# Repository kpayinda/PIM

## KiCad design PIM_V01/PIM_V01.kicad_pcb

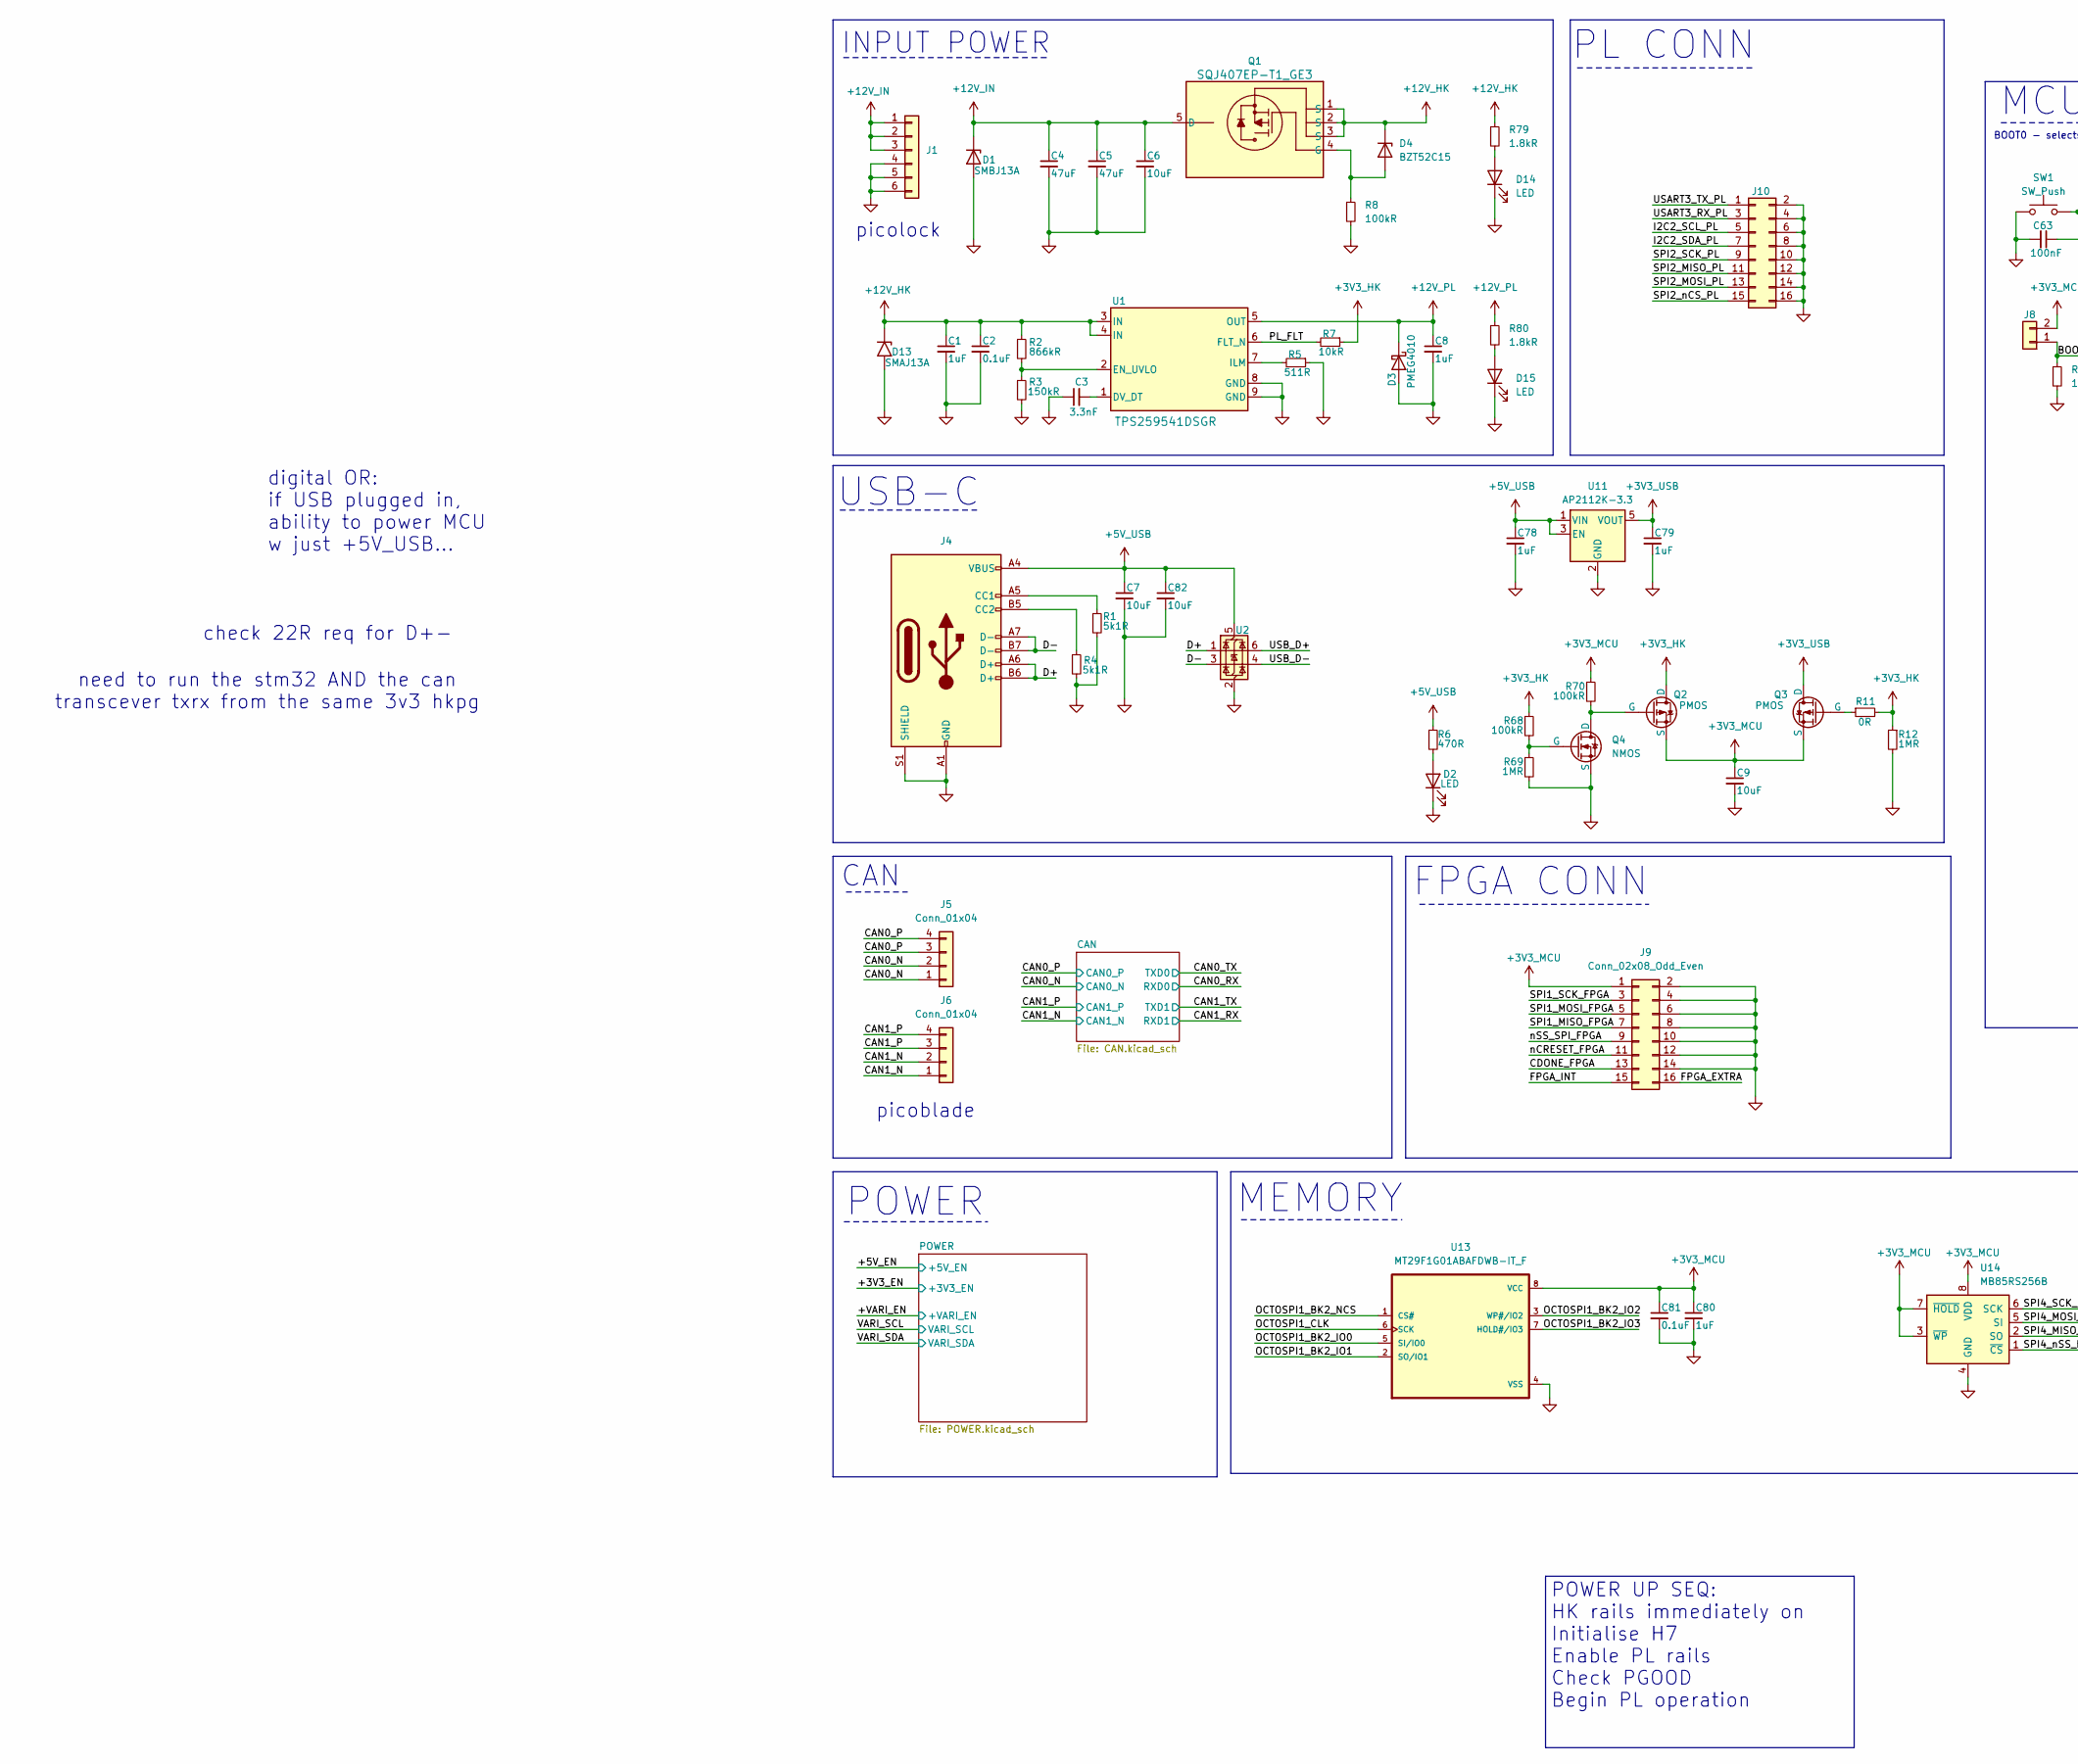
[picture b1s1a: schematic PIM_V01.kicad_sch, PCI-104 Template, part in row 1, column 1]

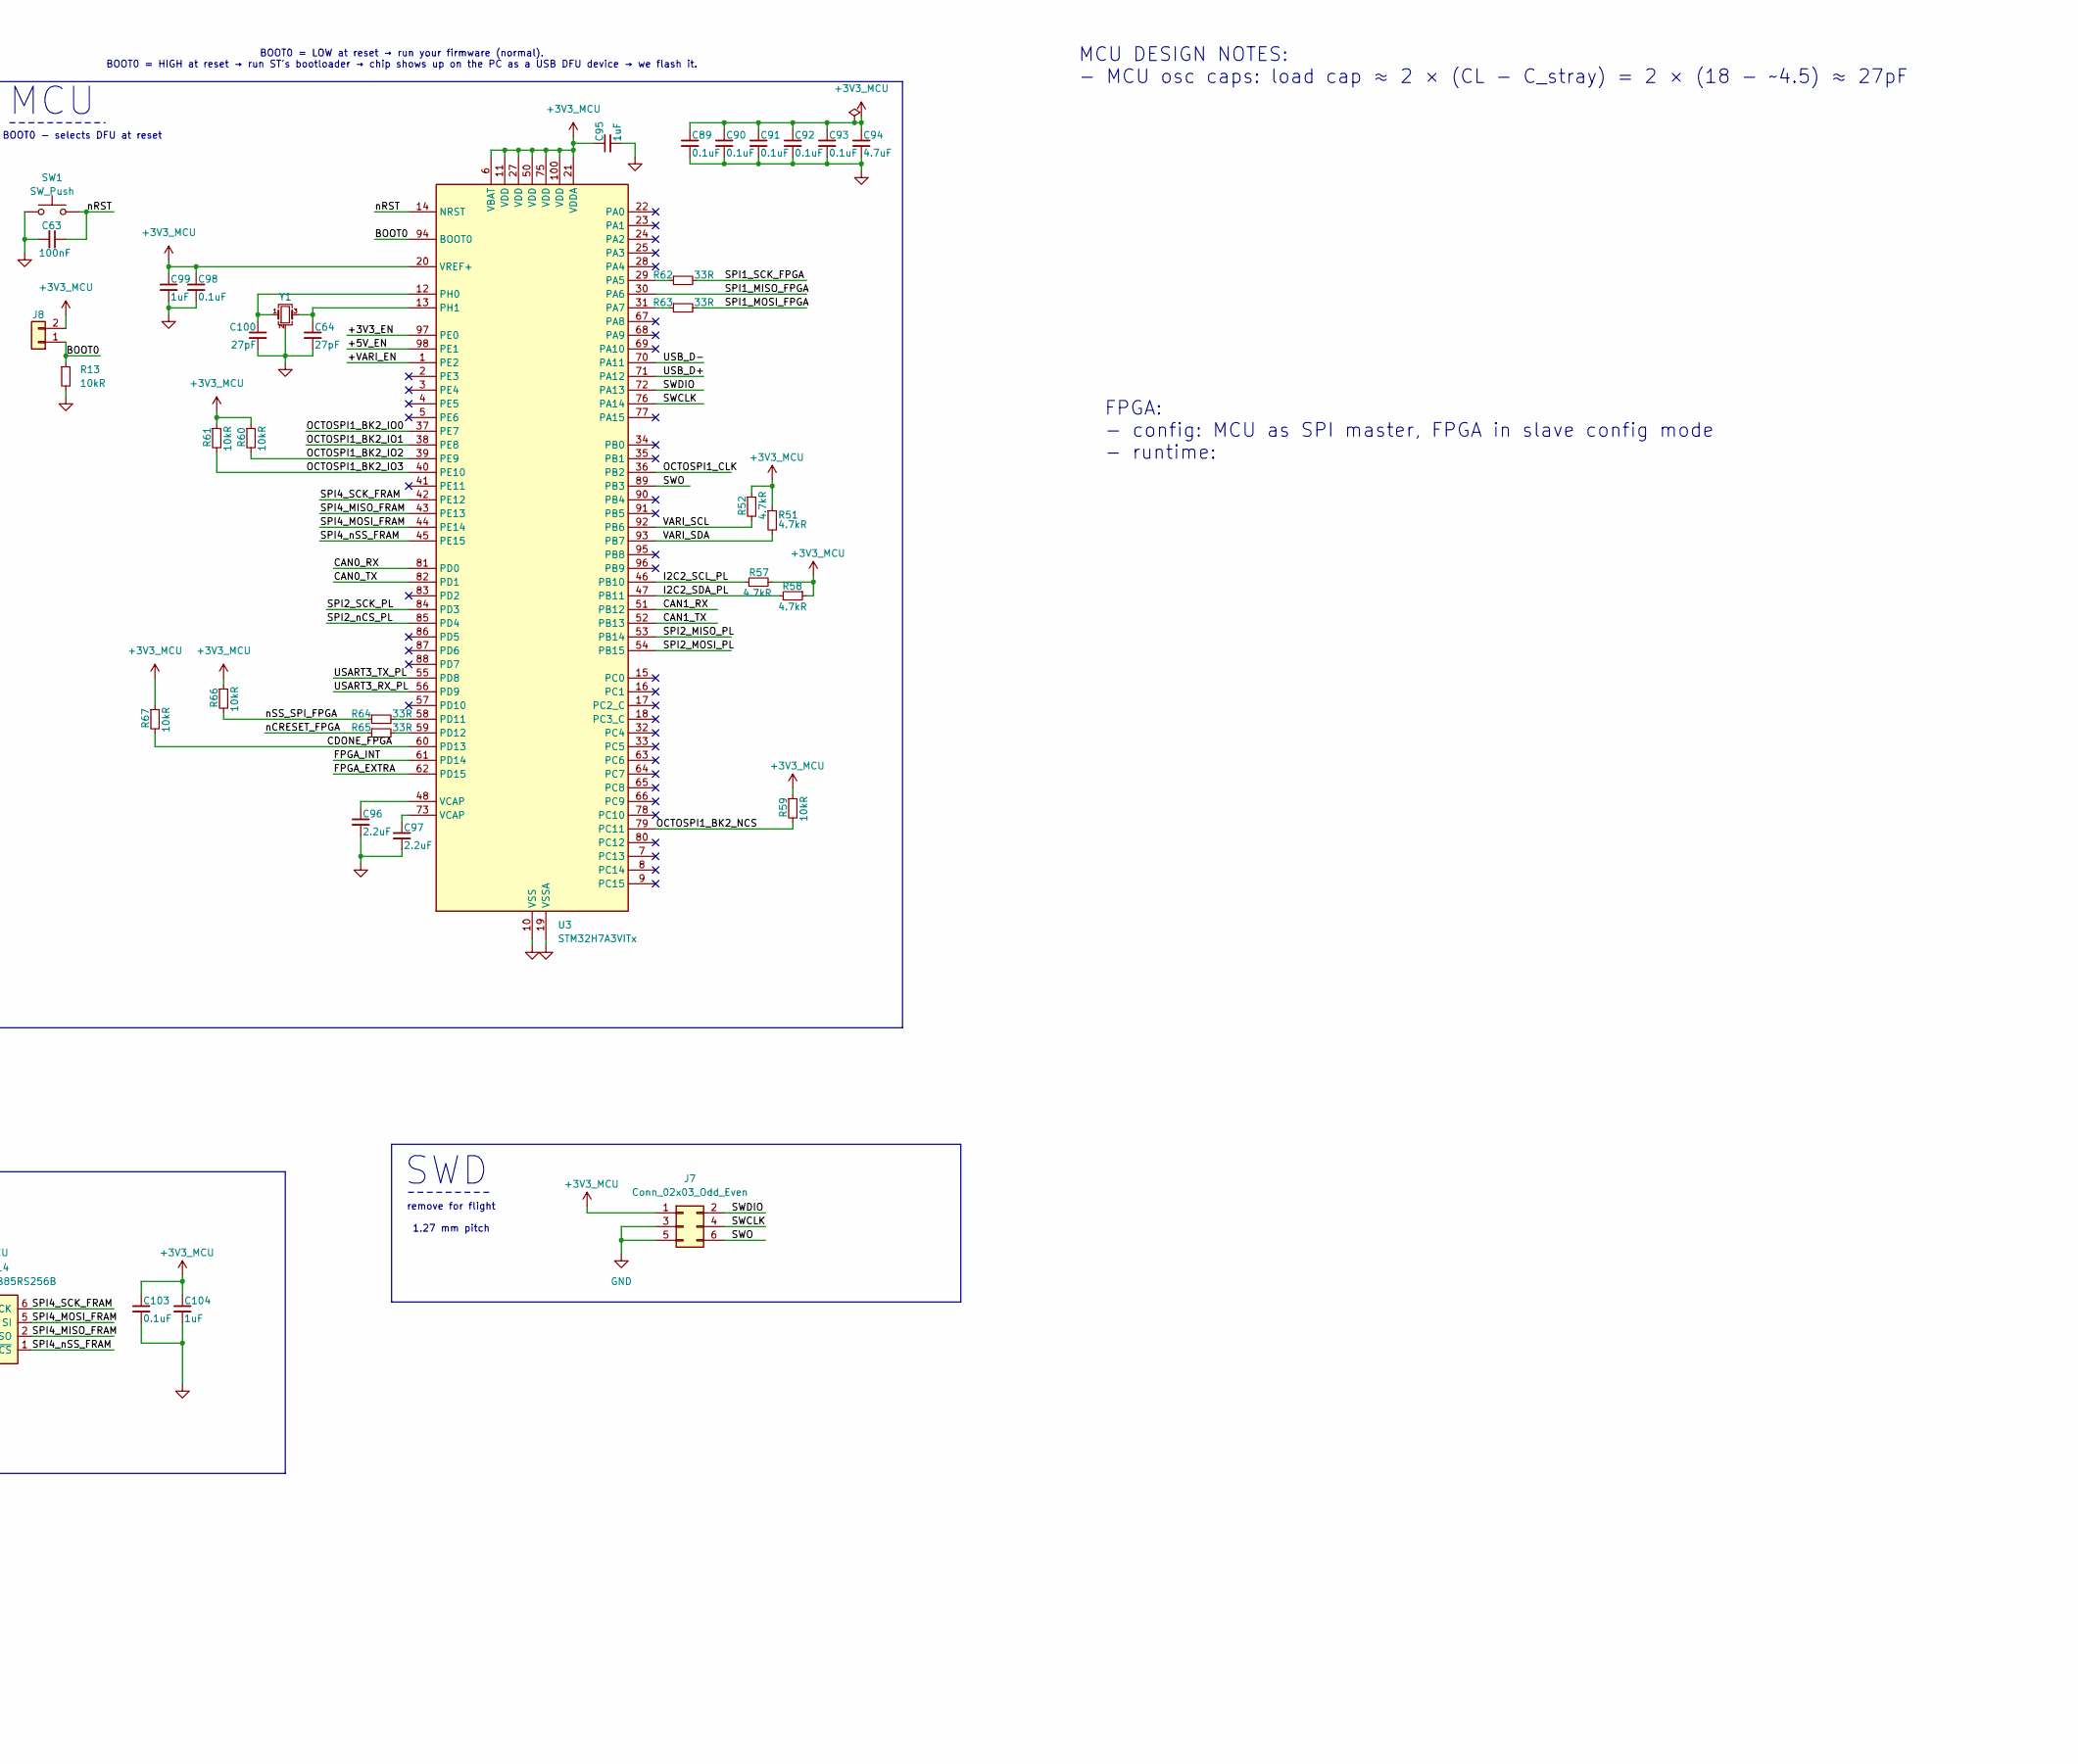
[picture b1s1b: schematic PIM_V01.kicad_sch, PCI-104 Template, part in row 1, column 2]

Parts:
C1, C8, C78, C79, C80, C95, C99, C104: 1uF; C_0603_1608Metric
C2, C81, C89, C90, C91, C92, C93, C98, C103: 0.1uF; C_0603_1608Metric
C3: 3.3nF; C_0603_1608Metric
C4, C5: 47uF; C_0603_1608Metric; Rating 50V, MLCC
C6, C7, C9, C82: 10uF; C_0603_1608Metric
C63: 100nF; C_0603_1608Metric
C64, C100: 27pF; C_0603_1608Metric
C94: 4.7uF; C_0603_1608Metric
C96, C97: 2.2uF; C_0603_1608Metric
D1: SMBJ13A; SMBJ16A; MPN SMBJ13A
D2: LED; LED_0603_1608Metric
D3: PMEG4010; Nexperia_CFP3_SOD-123W; MPN PMEG4010ER,115
D4: BZT52C15; Nexperia_CFP3_SOD-123W
D13: SMAJ13A; D_SMA; MPN SMAJ13A
D14, D15: LED; LED_0603_1608Metric; MPN XL-1608PGC-06
J1: Conn_01x06; Molex_Pico-Lock_504050-0691_1x06-1MP_P1.50mm_Horizontal; MPN 5040500691
J4: USB_C_Receptacle_USB2.0_14P; USB_C_Receptacle_HCTL_HC-TYPE-C-16P-01A
J5, J6: Conn_01x04; Molex_PicoBlade_53261-0471_1x04-1MP_P1.25mm_Horizontal
J7: Conn_02x03_Odd_Even; PinHeader_2x03_P2.54mm_Vertical
J8: Conn_01x02; PinHeader_1x02_P2.54mm_Vertical
J9, J10: Conn_02x08_Odd_Even; PinHeader_2x08_P2.54mm_Vertical
Q1: SQJ407EP-T1_GE3; PowerPAK-SO-8L_Option-2_VIS
Q2, Q3: PMOS; SOT-23-3; MPN DMG2305UX-7
Q4: NMOS; SOT-23-3
R1, R4: 5k1R; R_0603_1608Metric
R2: 866kR; R_0603_1608Metric
R3: 150kR; R_0603_1608Metric
R5: 511R; R_0603_1608Metric
R6: 470R; R_0603_1608Metric
R7, R13, R59, R60, R61, R66, R67: 10kR; R_0603_1608Metric
R8, R68, R70: 100kR; R_0603_1608Metric
R11: 0R; R_0603_1608Metric
R12, R69: 1MR; R_0603_1608Metric
R51, R52, R57, R58: 4.7kR; R_0603_1608Metric
R62, R63, R64, R65: 33R; R_0603_1608Metric
R79, R80: 1.8kR; R_0603_1608Metric
SW1: SW_Push; SW_SPST_B3U-1000P
U1: TPS259541DSGR; DSG0008A; MPN TPS259541DSGR
U2: USBLC6-2SC6; SOT-23-6
U3: STM32H7A3VITx; LQFP-100_14x14mm_P0.5mm
U11: AP2112K-3.3; SOT-23-5
U13: MT29F1G01ABAFDWB-IT_F; WSON-8-1EP_8x6mm_P1.27mm_EP3.4x4.3mm; PARTREV LTR
U14: MB85RS256B; JEITA_SOIC-8_3.9x4.9mm_P1.27mm
Y1: Crystal_GND24_Small; Crystal_SMD_Abracon_ABM8G-4Pin_3.2x2.5mm

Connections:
+3V3_HK: Q2.1 (D), R7.1, R11.2, R12.1, R68.1; also elsewhere on the board
+3V3_MCU: C9.1, C80.1, C81.1, C89.1, C90.1, C91.1, C92.1, C93.1, C94.1, C95.1, C98.1, C99.1, C103.1, C104.1, J7.1, J8.2, J9.1, Q2.3 (S), Q3.3 (S), R51.1, R52.1, R57.2, R58.1, R59.1, R60.1, R61.1, R66.1, R67.1, R70.1, U3.6 (VBAT), U3.11 (VDD), U3.20 (VREF+), U3.21 (VDDA), U3.27 (VDD), U3.50 (VDD), U3.75 (VDD), U3.100 (VDD), U13.8 (VCC), U14.3 (~WP), U14.7 (~HOLD), U14.8 (VDD)
+3V3_USB: C79.1, Q3.1 (D), U11.5 (VOUT)
+5V_USB: C7.1, C78.1, C82.1, J4.A4 (VBUS), J4.A9 (VBUS), J4.B4 (VBUS), J4.B9 (VBUS), R6.1, U2.5 (VBUS), U11.1 (VIN), U11.3 (EN)
+12V_HK: C1.1, C2.1, D4.1 (K), D13.1 (A1), Q1.1 (S), Q1.2 (S), Q1.3 (S), R2.1, R79.1, U1.3 (IN), U1.4 (IN); also elsewhere on the board
+12V_IN: C4.1, C5.1, C6.1, D1.1 (K), J1.1, J1.2, J1.3, Q1.5 (D)
+12V_PL: C8.1, D3.1 (K), R80.1, U1.5 (OUT); also elsewhere on the board
/+3V3_EN: U3.97 (PE0); also elsewhere on the board
/+5V_EN: U3.98 (PE1); also elsewhere on the board
/+VARI_EN: U3.1 (PE2); also elsewhere on the board
/BOOT0: J8.1, R13.1, U3.94 (BOOT0)
/CAN0_N: J5.1, J5.2; also elsewhere on the board
/CAN0_P: J5.3, J5.4; also elsewhere on the board
/CAN0_RX: U3.81 (PD0); also elsewhere on the board
/CAN0_TX: U3.82 (PD1); also elsewhere on the board
/CAN1_N: J6.1, J6.2; also elsewhere on the board
/CAN1_P: J6.3, J6.4; also elsewhere on the board
/CAN1_RX: U3.51 (PB12); also elsewhere on the board
/CAN1_TX: U3.52 (PB13); also elsewhere on the board
/CDONE_FPGA: J9.13, R67.2, U3.60 (PD13)
/D+: J4.A6 (D+), J4.B6 (D+), U2.1 (I/O1)
/D-: J4.A7 (D-), J4.B7 (D-), U2.3 (I/O2)
/FPGA_EXTRA: J9.16, U3.62 (PD15)
/FPGA_INT: J9.15, U3.61 (PD14)
/I2C2_SCL_PL: J10.5, R57.1, U3.46 (PB10)
/I2C2_SDA_PL: J10.7, R58.2, U3.47 (PB11)
/OCTOSPI1_BK2_IO0: U3.37 (PE7), U13.5 (SI/IO0)
/OCTOSPI1_BK2_IO1: U3.38 (PE8), U13.2 (SO/IO1)
/OCTOSPI1_BK2_IO2: R60.2, U3.39 (PE9), U13.3 (WP#/IO2)
/OCTOSPI1_BK2_IO3: R61.2, U3.40 (PE10), U13.7 (HOLD#/IO3)
/OCTOSPI1_BK2_NCS: R59.2, U3.79 (PC11), U13.1 (CS#)
/OCTOSPI1_CLK: U3.36 (PB2), U13.6 (SCK)
/PL_FLT: R7.2, U1.6 (FLT_N)
/SPI1_MISO_FPGA: J9.7, U3.30 (PA6)
/SPI1_MOSI_FPGA: J9.5, R63.2
/SPI1_SCK_FPGA: J9.3, R62.2
/SPI2_MISO_PL: J10.11, U3.53 (PB14)
/SPI2_MOSI_PL: J10.13, U3.54 (PB15)
/SPI2_SCK_PL: J10.9, U3.84 (PD3)
/SPI2_nCS_PL: J10.15, U3.85 (PD4)
/SPI4_MISO_FRAM: U3.43 (PE13), U14.2 (SO)
/SPI4_MOSI_FRAM: U3.44 (PE14), U14.5 (SI)
/SPI4_SCK_FRAM: U3.42 (PE12), U14.6 (SCK)
/SPI4_nSS_FRAM: U3.45 (PE15), U14.1 (~CS)
/SWCLK: J7.4, U3.76 (PA14)
/SWDIO: J7.2, U3.72 (PA13)
/SWO: J7.6, U3.89 (PB3)
/USART3_RX_PL: J10.3, U3.56 (PD9)
/USART3_TX_PL: J10.1, U3.55 (PD8)
/USB_D+: U2.6 (I/O1), U3.71 (PA12)
/USB_D-: U2.4 (I/O2), U3.70 (PA11)
/VARI_SCL: R52.2, U3.92 (PB6); also elsewhere on the board
/VARI_SDA: R51.2, U3.93 (PB7); also elsewhere on the board
/nCRESET_FPGA: J9.11, R65.1
/nRST: C63.1, SW1.2, U3.14 (NRST)
/nSS_SPI_FPGA: J9.9, R64.1, R66.2
GND: C1.2, C2.2, C3.1, C4.2, C5.2, C6.2, C7.2, C8.2, C9.2, C63.2, C64.2, C78.2, C79.2, C80.2, C81.2, C82.2, C89.2, C90.2, C91.2, C92.2, C93.2, C94.2, C95.2, C96.2, C97.2, C98.2, C99.2, C100.2, C103.2, C104.2, D1.2 (A), D2.1 (K), D3.2 (A), D13.2 (A2), D14.1 (K), D15.1 (K), J1.4, J1.5, J1.6, J4.A1 (GND), J4.A12 (GND), J4.B1 (GND), J4.B12 (GND), J4.S1 (SHIELD), J7.3, J7.5, J9.2, J9.4, J9.6, J9.8, J9.10, J9.12, J9.14, J10.2, J10.4, J10.6, J10.8, J10.10, J10.12, J10.14, J10.16, Q4.3 (S), R1.2, R3.2, R4.2, R5.1, R8.2, R12.2, R13.2, R69.2, SW1.1, U1.8 (GND), U1.9 (GND), U2.2 (GND), U3.10 (VSS), U3.19 (VSSA), U3.26 (VSS), U3.49 (VSS), U3.74 (VSS), U3.99 (VSS), U11.2 (GND), U13.4 (VSS), U14.4 (GND), Y1.2 (G), Y1.4 (G); also elsewhere on the board
unnamed: C96.1, U3.48 (VCAP)
unnamed: C97.1, U3.73 (VCAP)
unnamed: D2.2 (A), R6.2
unnamed: D4.2 (A), Q1.4 (G), R8.1
unnamed: D14.2 (A), R79.2
unnamed: D15.2 (A), R80.2
unnamed: J4.A5 (CC1), R1.1
unnamed: J4.B5 (CC2), R4.1
unnamed: Q2.2 (G), Q4.1 (D), R70.2
unnamed: Q3.2 (G), R11.1
unnamed: Q4.2 (G), R68.2, R69.1
unnamed: C3.2, U1.1 (DV_DT)
unnamed: R2.2, R3.1, U1.2 (EN_UVLO)
unnamed: R5.2, U1.7 (ILM)
unnamed: R62.1, U3.29 (PA5)
unnamed: R63.1, U3.31 (PA7)
unnamed: R64.2, U3.58 (PD11)
unnamed: R65.2, U3.59 (PD12)
unnamed: C100.1, U3.12 (PH0), Y1.1
unnamed: C64.1, U3.13 (PH1), Y1.3

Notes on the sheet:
need to run the stm32 AND the can transcever txrx from the same 3v3 hkpg
BOOT0 - selects DFU at reset
picoblade
BOOT0 = LOW at reset → run your firmware (normal). BOOT0 = HIGH at reset → run ST's bootloader → chip shows up on the PC as a USB DFU device → we flash it.
FPGA CONN
remove for flight 1.27 mm pitch
USB-C
POWER
MCU DESIGN NOTES: - MCU osc caps: load cap ≈ 2 × (CL − C_stray) = 2 × (18 − ~4.5) ≈ 27pF
digital OR: if USB plugged in, ability to power MCU w just +5V_USB...
PL CONN
check 22R req for D+-
MCU
picolock
FPGA: - config: MCU as SPI master, FPGA in slave config mode - runtime:
INPUT POWER
CAN
MEMORY
SWD
POWER UP SEQ: HK rails immediately on Initialise H7 Enable PL rails Check PGOOD Begin PL operation

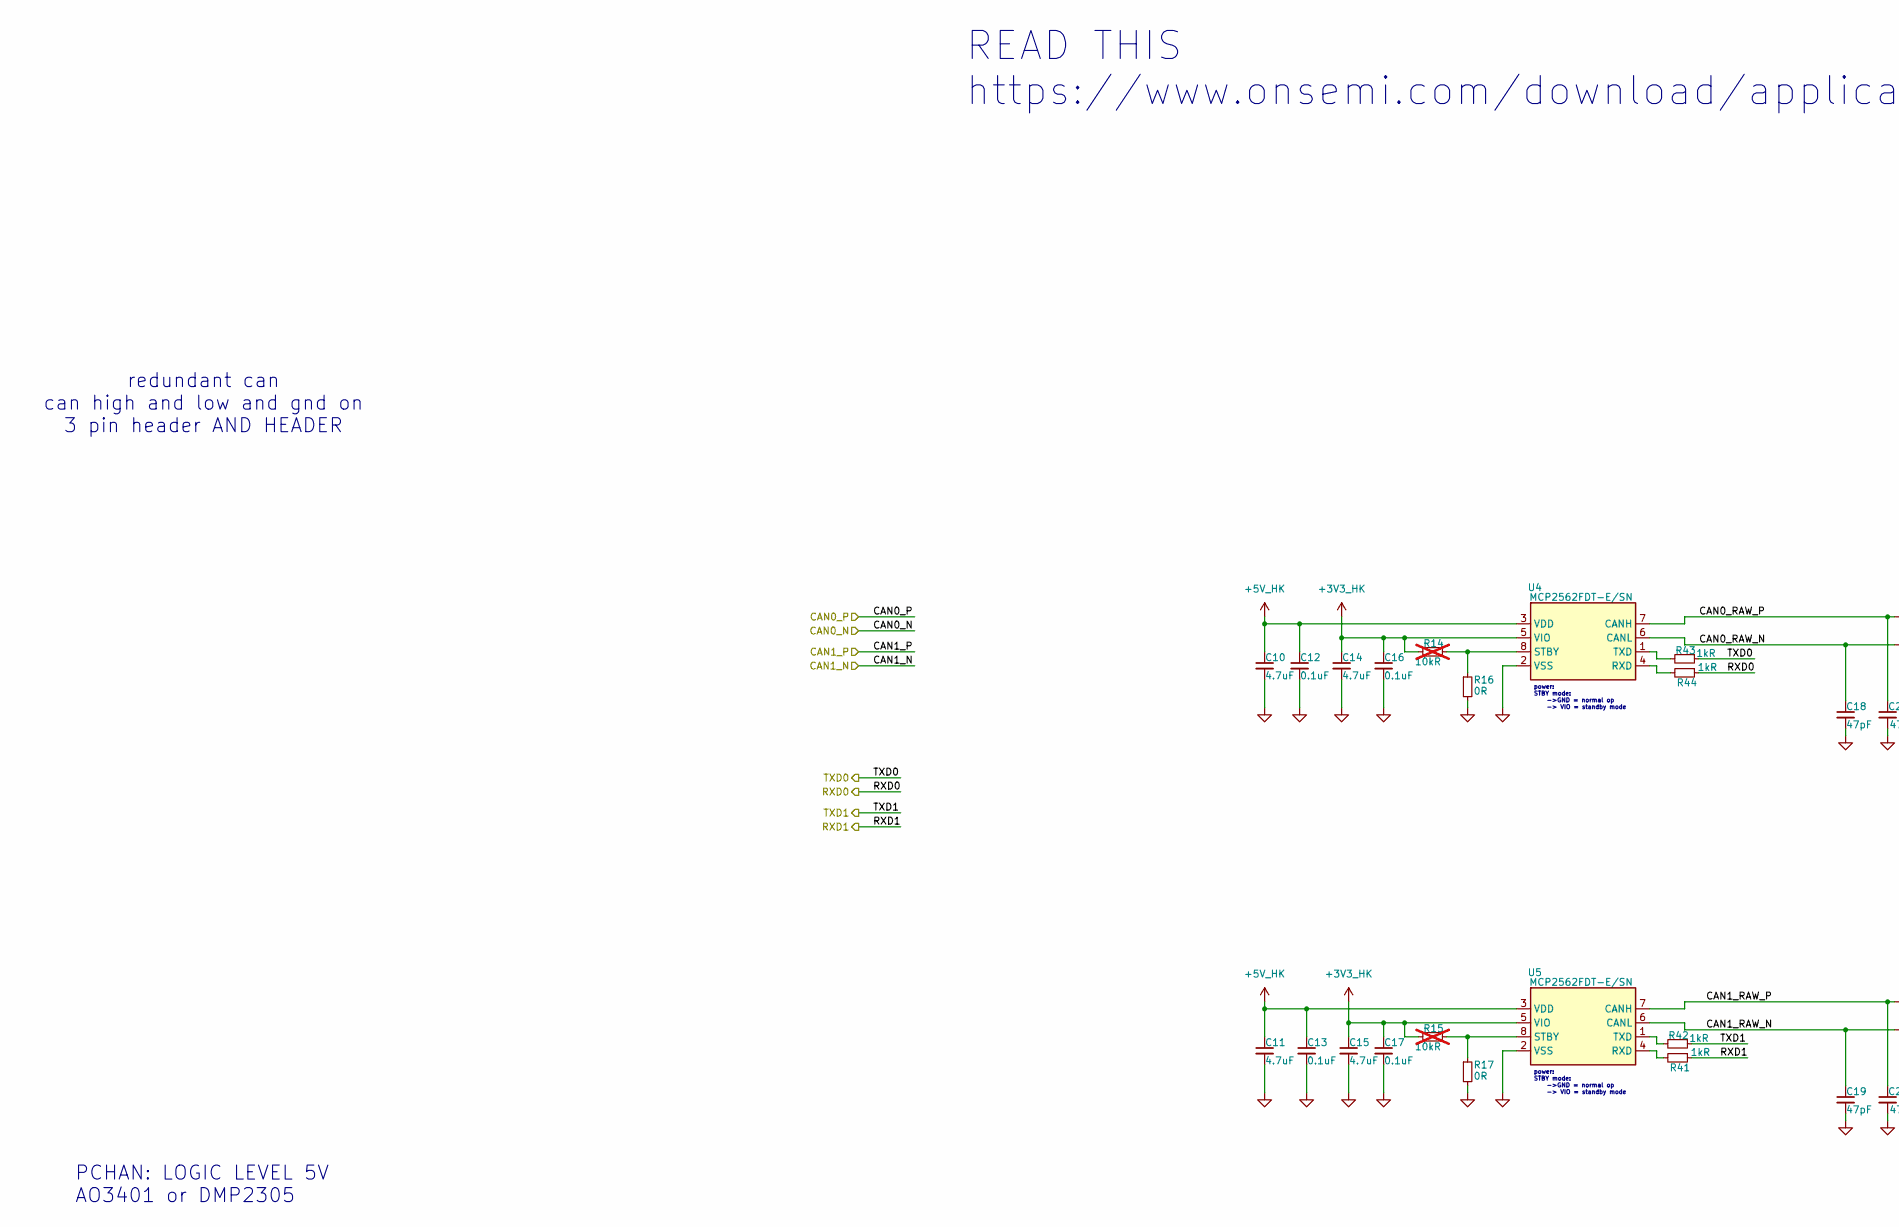
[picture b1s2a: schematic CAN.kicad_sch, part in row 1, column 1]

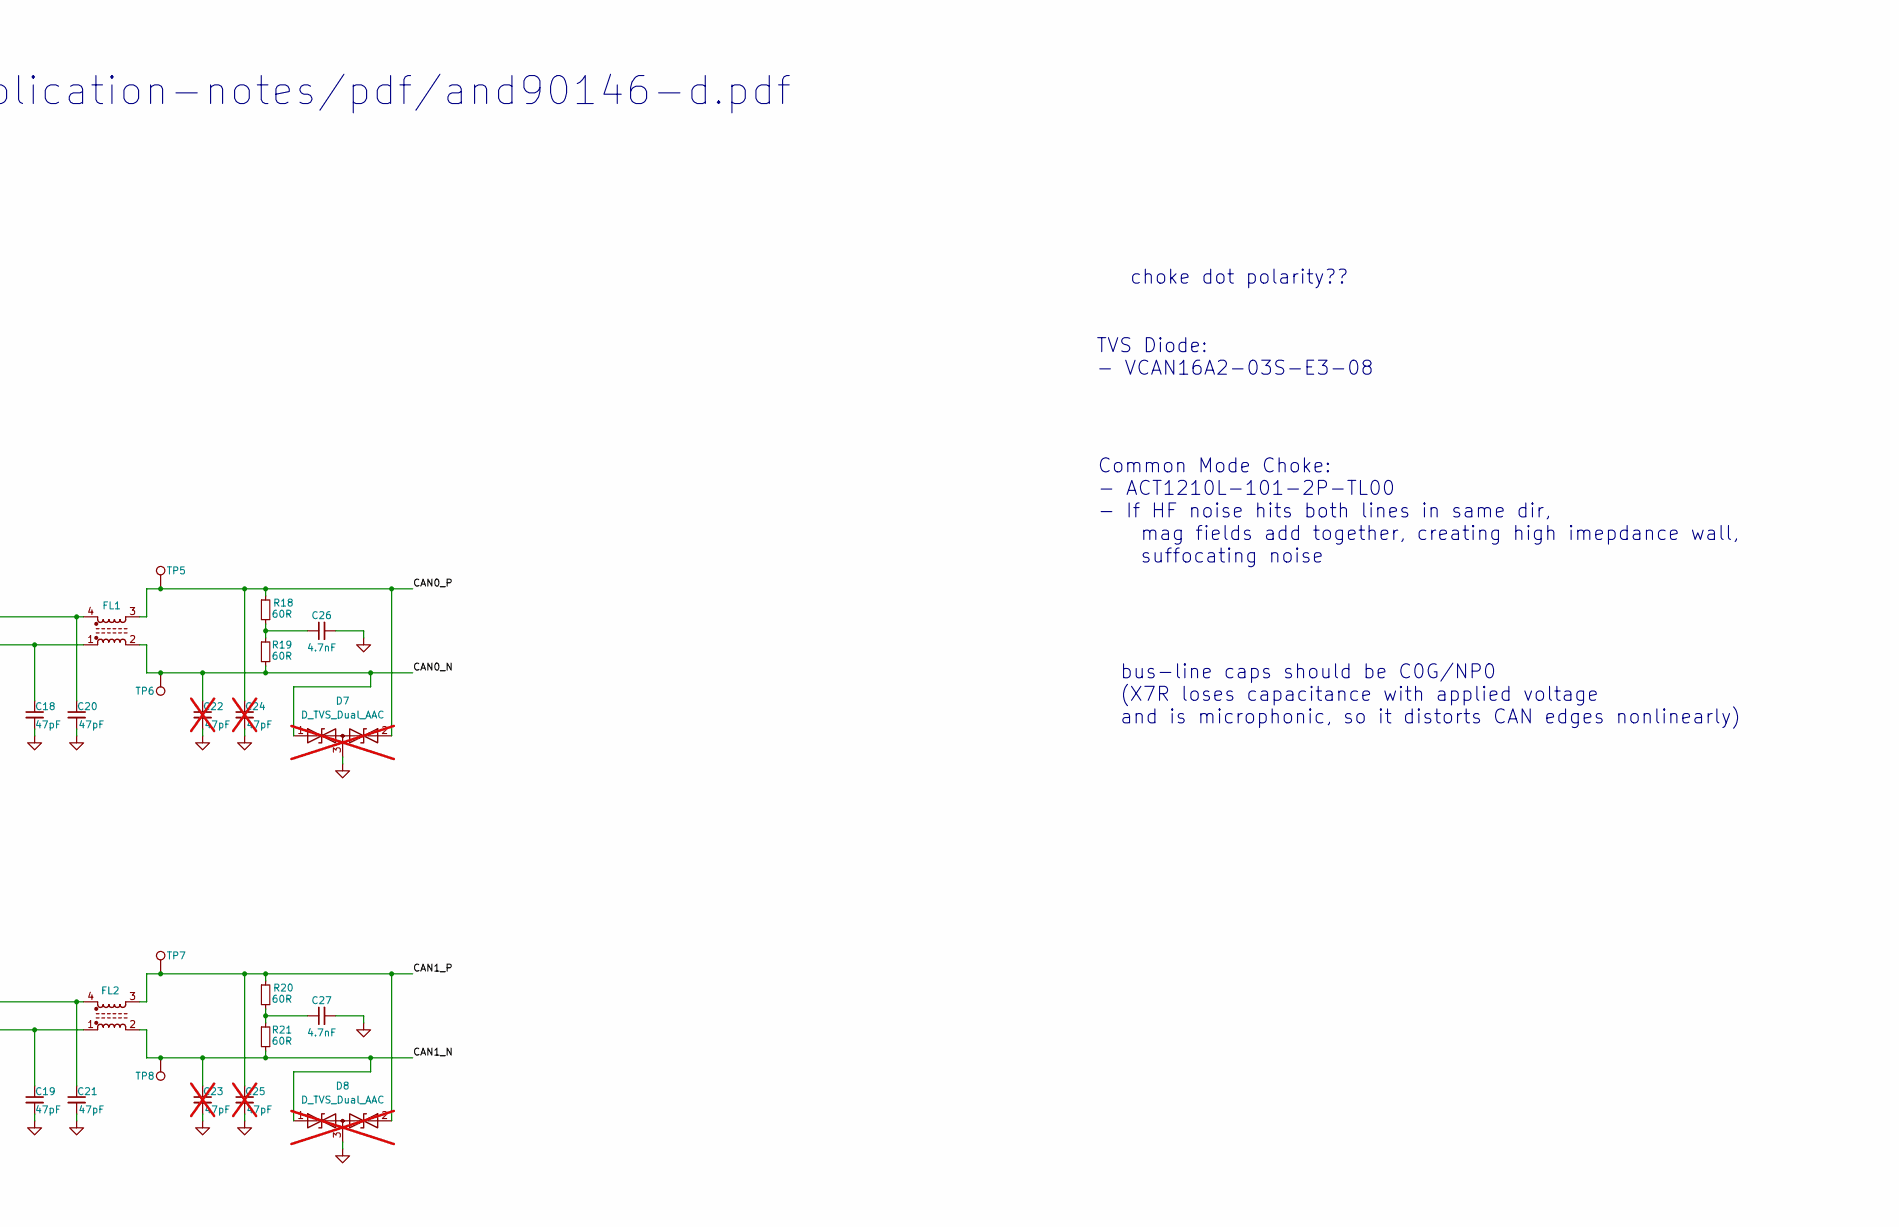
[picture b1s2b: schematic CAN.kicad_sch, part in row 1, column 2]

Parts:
C10, C11, C14, C15: 4.7uF; C_0603_1608Metric
C12, C13, C16, C17: 0.1uF; C_0603_1608Metric
C18, C19, C20, C21: 47pF; C_0603_1608Metric
C22, C23, C24, C25: 47pF; C_0603_1608Metric; not fitted
C26, C27: 4.7nF; C_0603_1608Metric
D7, D8: D_TVS_Dual_AAC; SOT-23-3; not fitted
FL1, FL2: Choke_CommonMode_FerriteCore_1243; L_CommonModeChoke_Coilcraft_1812CAN
R14, R15: 10kR; R_0603_1608Metric; not fitted
R16, R17: 0R; R_0603_1608Metric
R18, R19, R20, R21: 60R; R_0603_1608Metric
R41, R42, R43, R44: 1kR; R_0603_1608Metric
TP5, TP6, TP7, TP8: TestPoint; TestPoint_Keystone_5000-5004_Miniature
U4, U5: MCP2562FDT-E/SN; SOIC-8_3.9x4.9mm_P1.27mm

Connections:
+3V3_HK: C14.1, C15.1, C16.1, C17.1, R14.2, R15.2, U4.5 (VIO), U5.5 (VIO); also elsewhere on the board
+5V_HK: C10.1, C11.1, C12.1, C13.1, U4.3 (VDD), U5.3 (VDD); also elsewhere on the board
/CAN0_N: C22.1, D7.1 (A1), FL1.2, R19.2, TP6.1; also elsewhere on the board
/CAN0_P: C24.1, D7.2 (A2), FL1.3, R18.1, TP5.1; also elsewhere on the board
/CAN0_RX: R44.1; also elsewhere on the board
/CAN0_TX: R43.1; also elsewhere on the board
/CAN1_N: C23.1, D8.1 (A1), FL2.2, R21.2, TP8.1; also elsewhere on the board
/CAN1_P: C25.1, D8.2 (A2), FL2.3, R20.1, TP7.1; also elsewhere on the board
/CAN1_RX: R41.1; also elsewhere on the board
/CAN1_TX: R42.1; also elsewhere on the board
/CAN/CAN0_RAW_N: C18.1, FL1.1, U4.6 (CANL)
/CAN/CAN0_RAW_P: C20.1, FL1.4, U4.7 (CANH)
/CAN/CAN1_RAW_N: C19.1, FL2.1, U5.6 (CANL)
/CAN/CAN1_RAW_P: C21.1, FL2.4, U5.7 (CANH)
GND: C10.2, C11.2, C12.2, C13.2, C14.2, C15.2, C16.2, C17.2, C18.2, C19.2, C20.2, C21.2, C22.2, C23.2, C24.2, C25.2, C26.2, C27.2, D7.3 (common), D8.3 (common), R16.2, R17.2, U4.2 (VSS), U5.2 (VSS); also elsewhere on the board
unnamed: C26.1, R18.2, R19.1
unnamed: C27.1, R20.2, R21.1
unnamed: R44.2, U4.4 (RXD)
unnamed: R14.1, R16.1, U4.8 (STBY)
unnamed: R43.2, U4.1 (TXD)
unnamed: R41.2, U5.4 (RXD)
unnamed: R15.1, R17.1, U5.8 (STBY)
unnamed: R42.2, U5.1 (TXD)

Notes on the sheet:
choke dot polarity??
bus-line caps should be C0G/NP0 (X7R loses capacitance with applied voltage and is microphonic, so it distorts CAN edges nonlinearly)
TVS Diode: - VCAN16A2-03S-E3-08
Common Mode Choke: - ACT1210L-101-2P-TL00 - If HF noise hits both lines in same dir, mag fields add together, creating high imepdance wall, suffocating noise
power: STBY mode: ->GND = normal op -> VIO = standby mode
PCHAN: LOGIC LEVEL 5V AO3401 or DMP2305
redundant can can high and low and gnd on 3 pin header AND HEADER
READ THIS https://www.onsemi.com/download/application-notes/pdf/and90146-d.pdf
